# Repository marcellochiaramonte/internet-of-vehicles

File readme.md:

Internet of Vehicles Project to bring IoT into Electric Vehicles

➡️ [Micropython Pycom Module Code](./2_Software_Module)

➡️ [Fullstack Web App Springboot Angular](./3_Software_Cloud/iov-full-stack-app)

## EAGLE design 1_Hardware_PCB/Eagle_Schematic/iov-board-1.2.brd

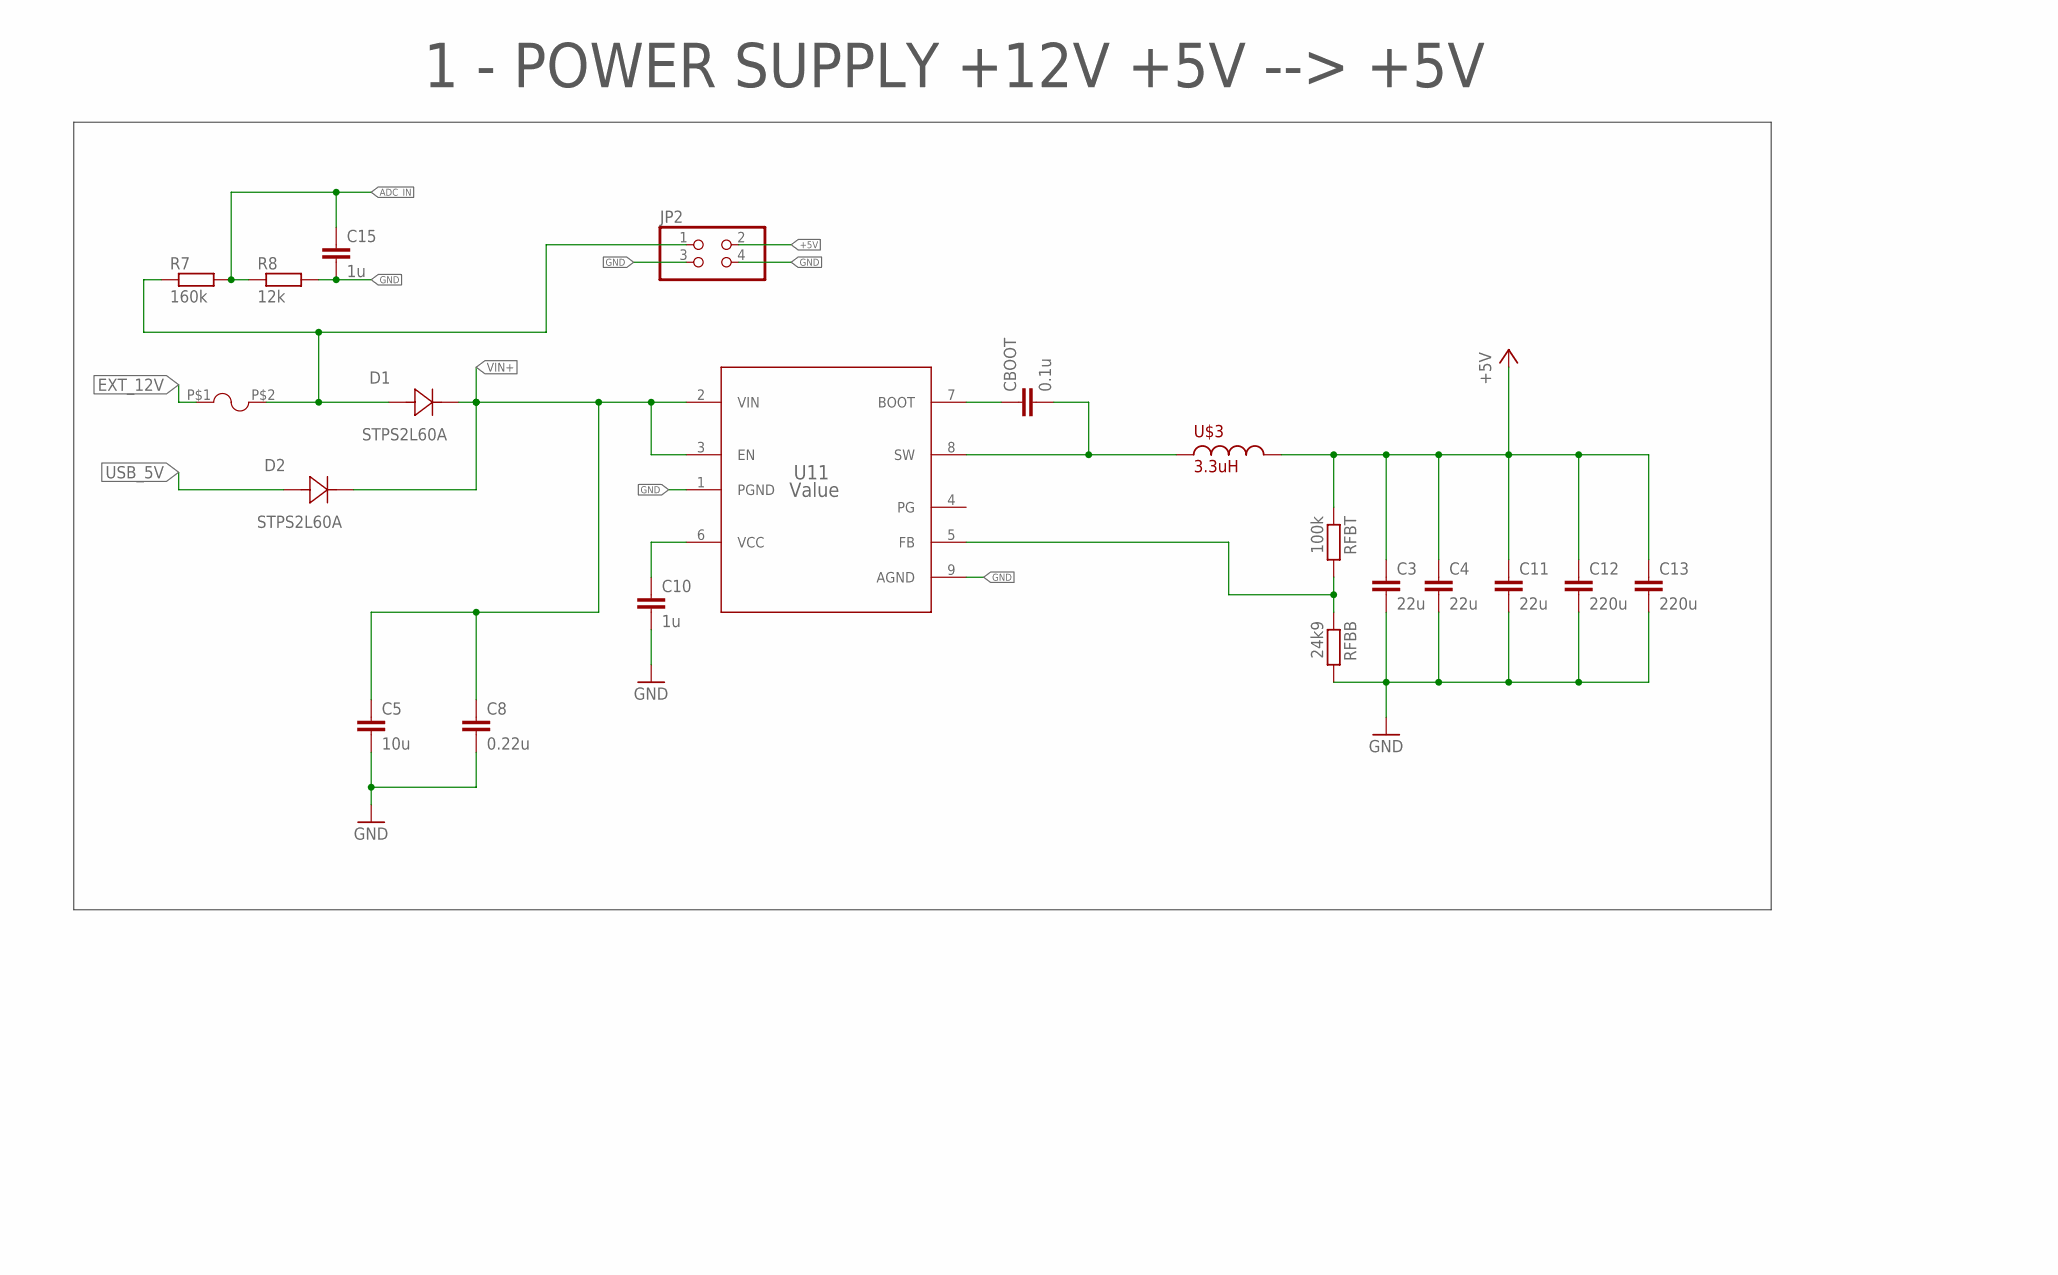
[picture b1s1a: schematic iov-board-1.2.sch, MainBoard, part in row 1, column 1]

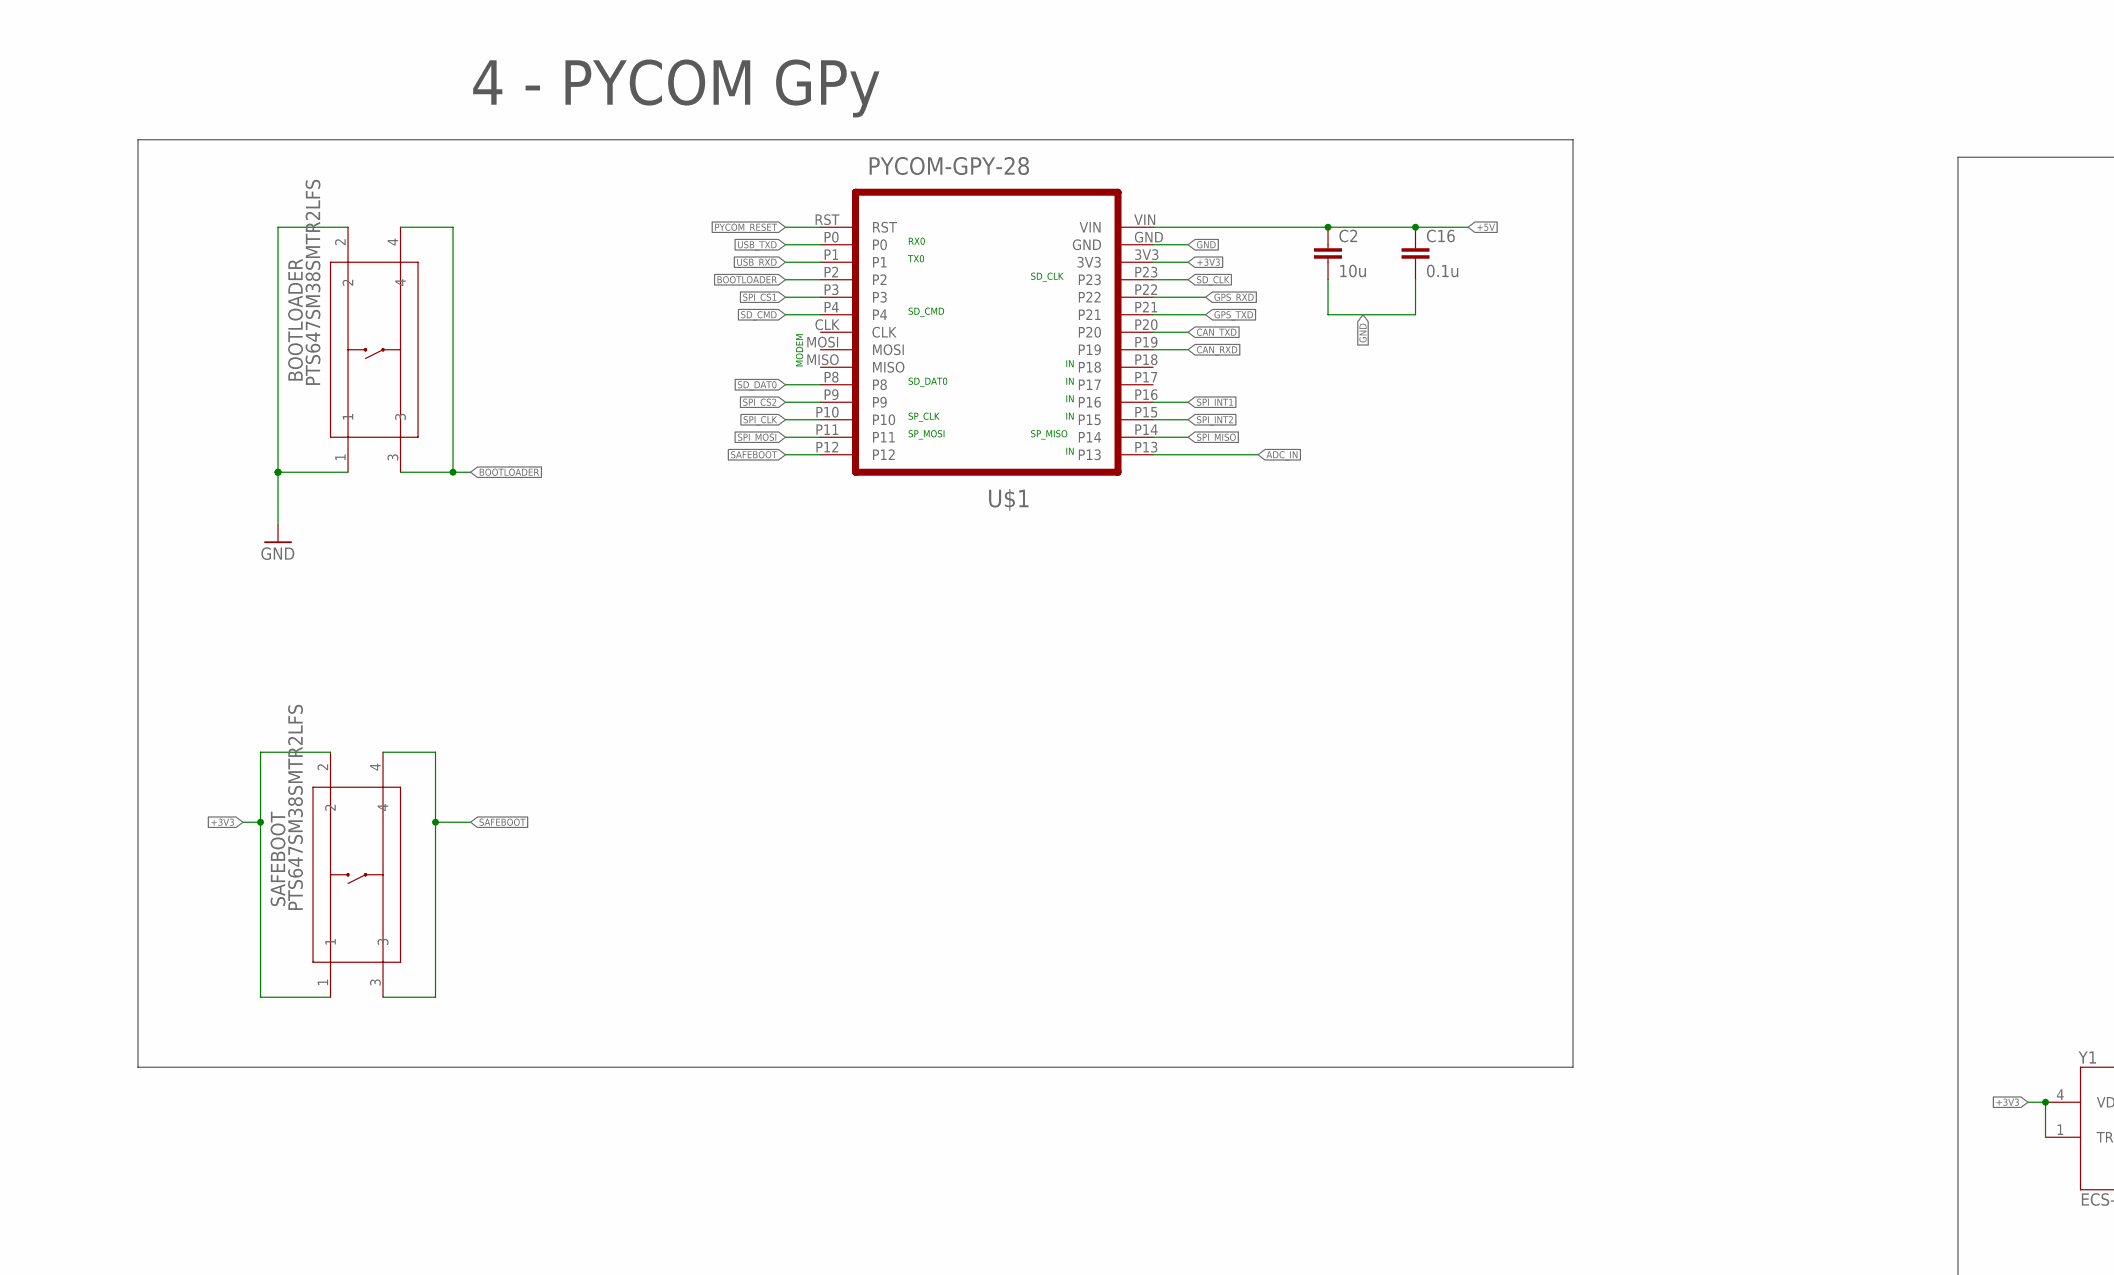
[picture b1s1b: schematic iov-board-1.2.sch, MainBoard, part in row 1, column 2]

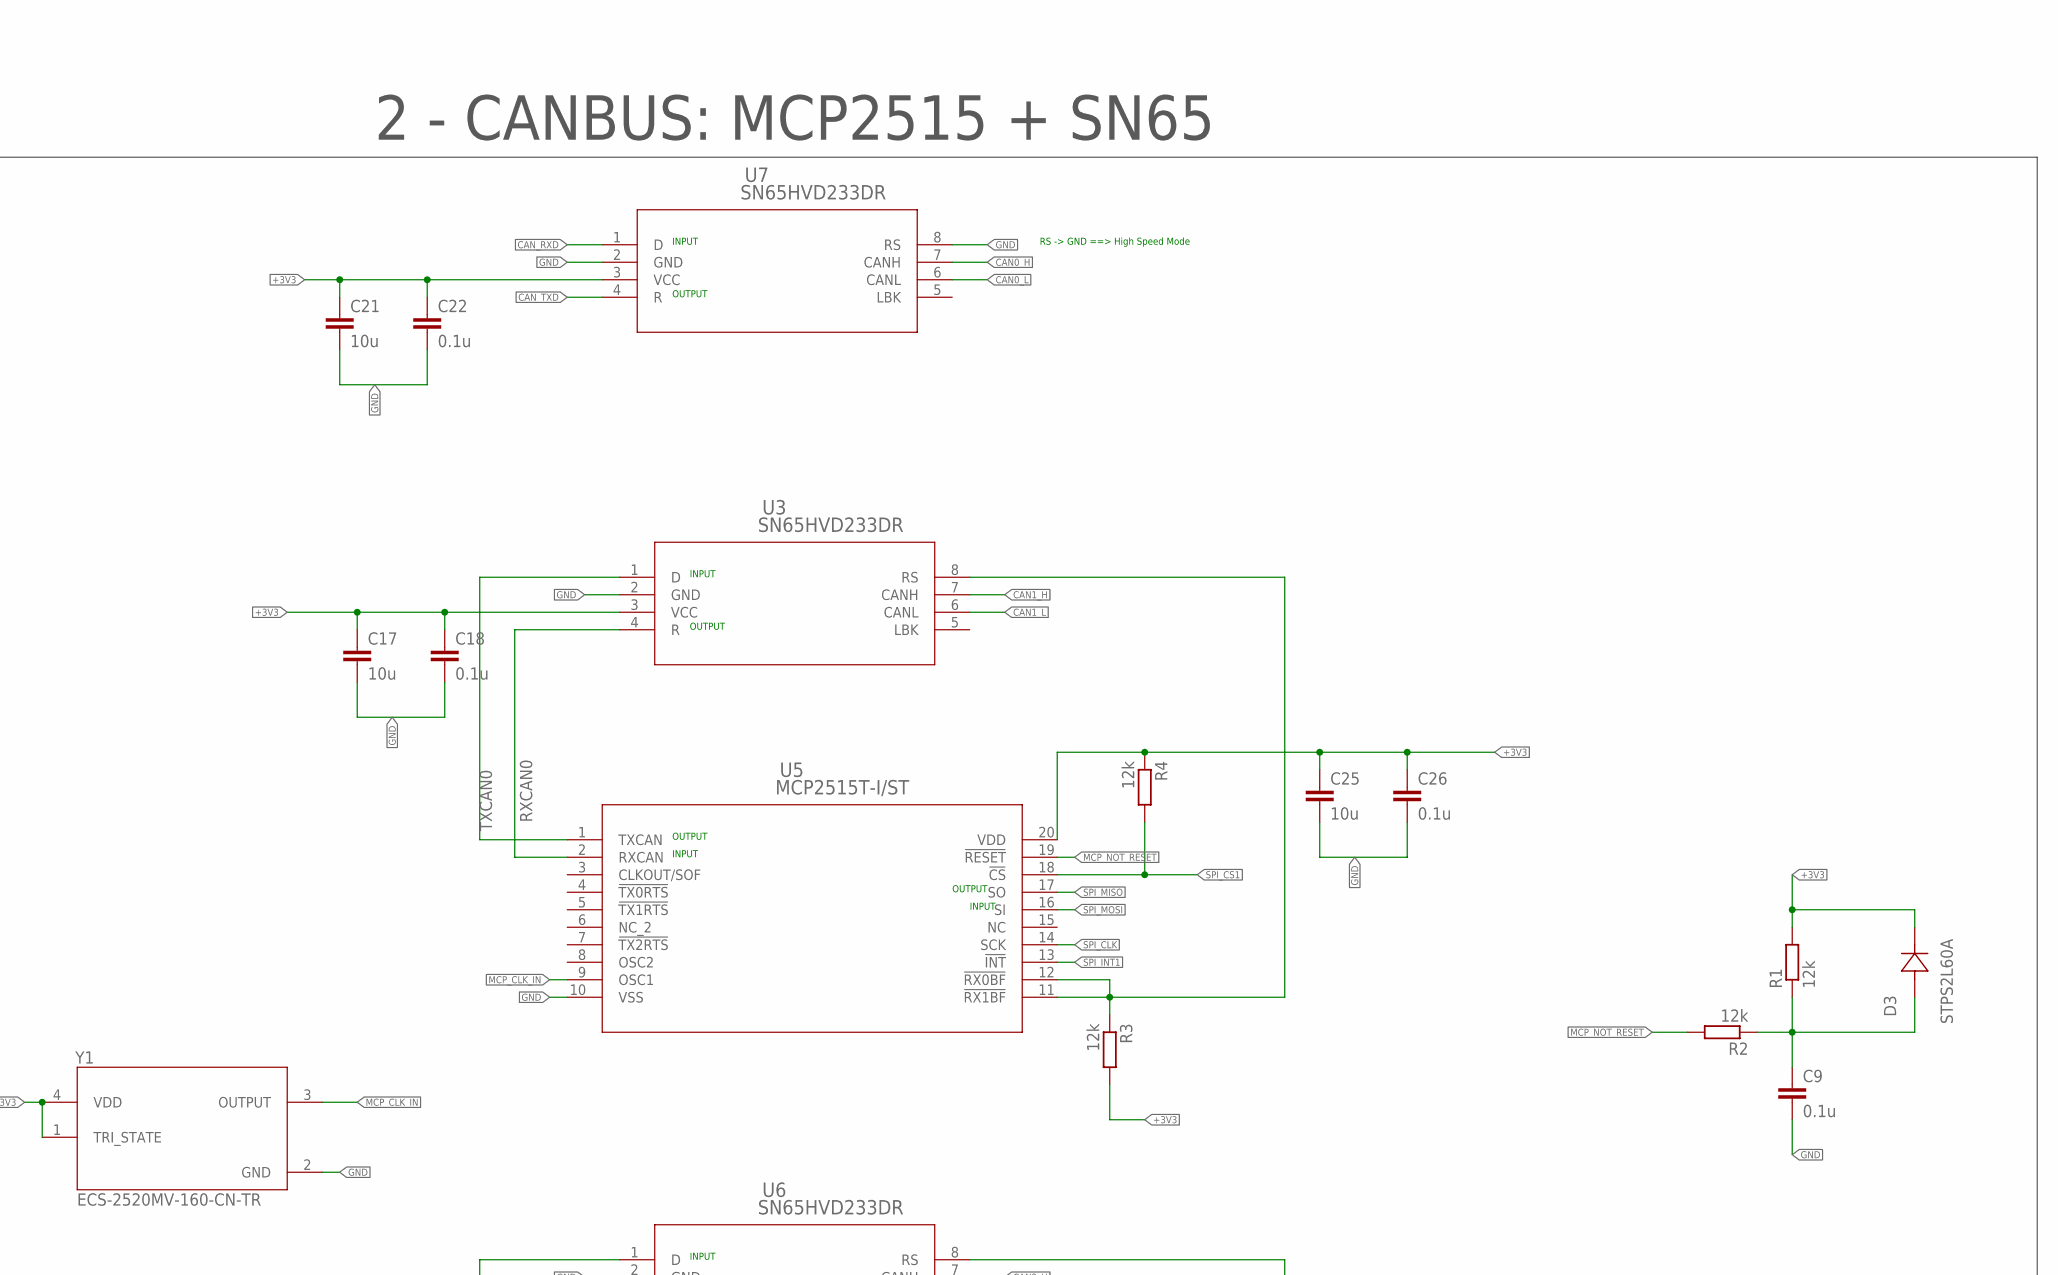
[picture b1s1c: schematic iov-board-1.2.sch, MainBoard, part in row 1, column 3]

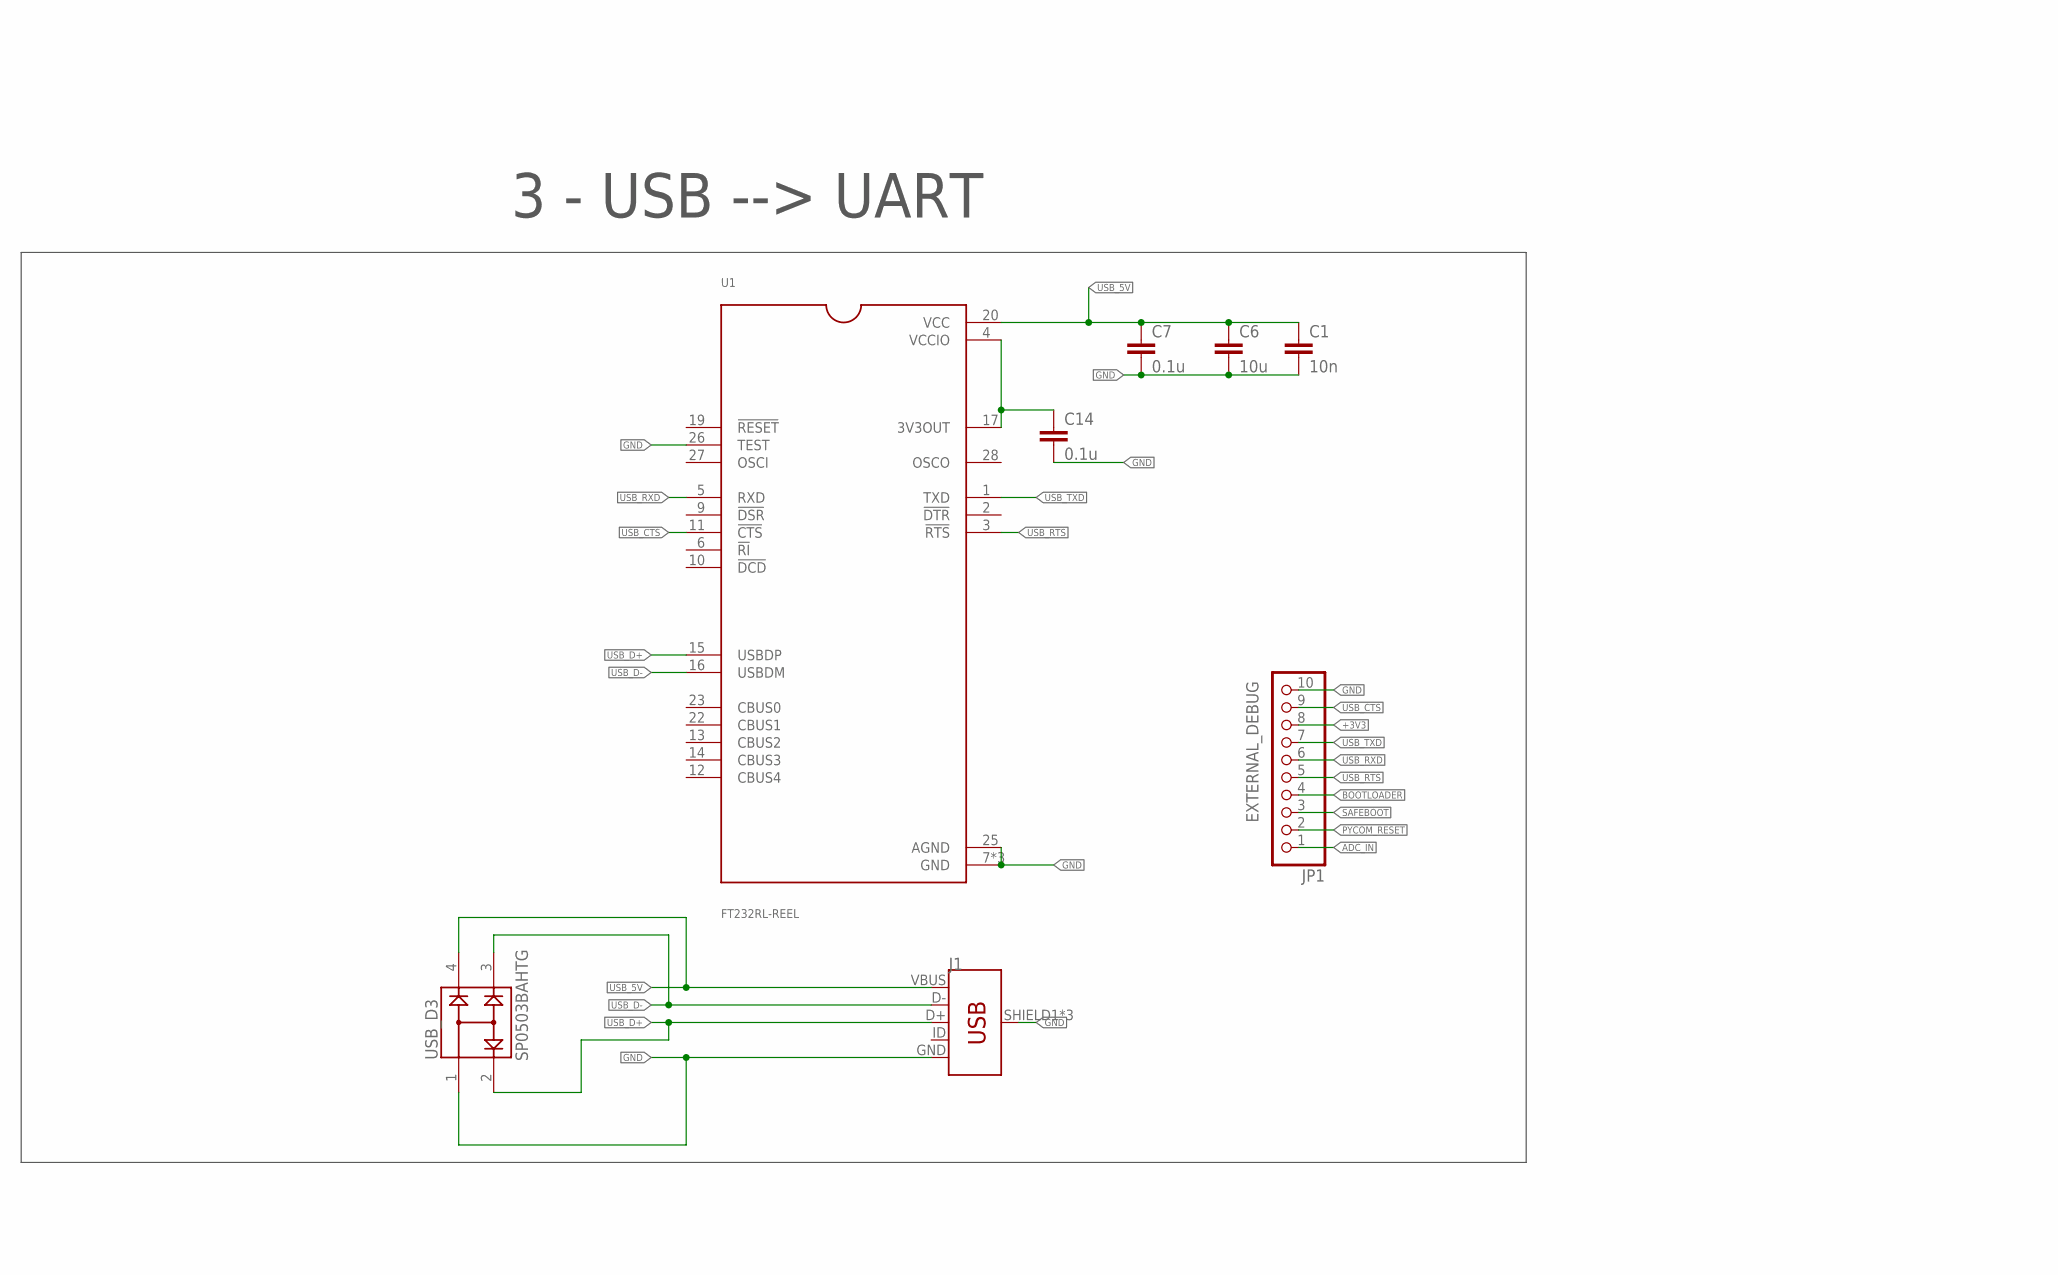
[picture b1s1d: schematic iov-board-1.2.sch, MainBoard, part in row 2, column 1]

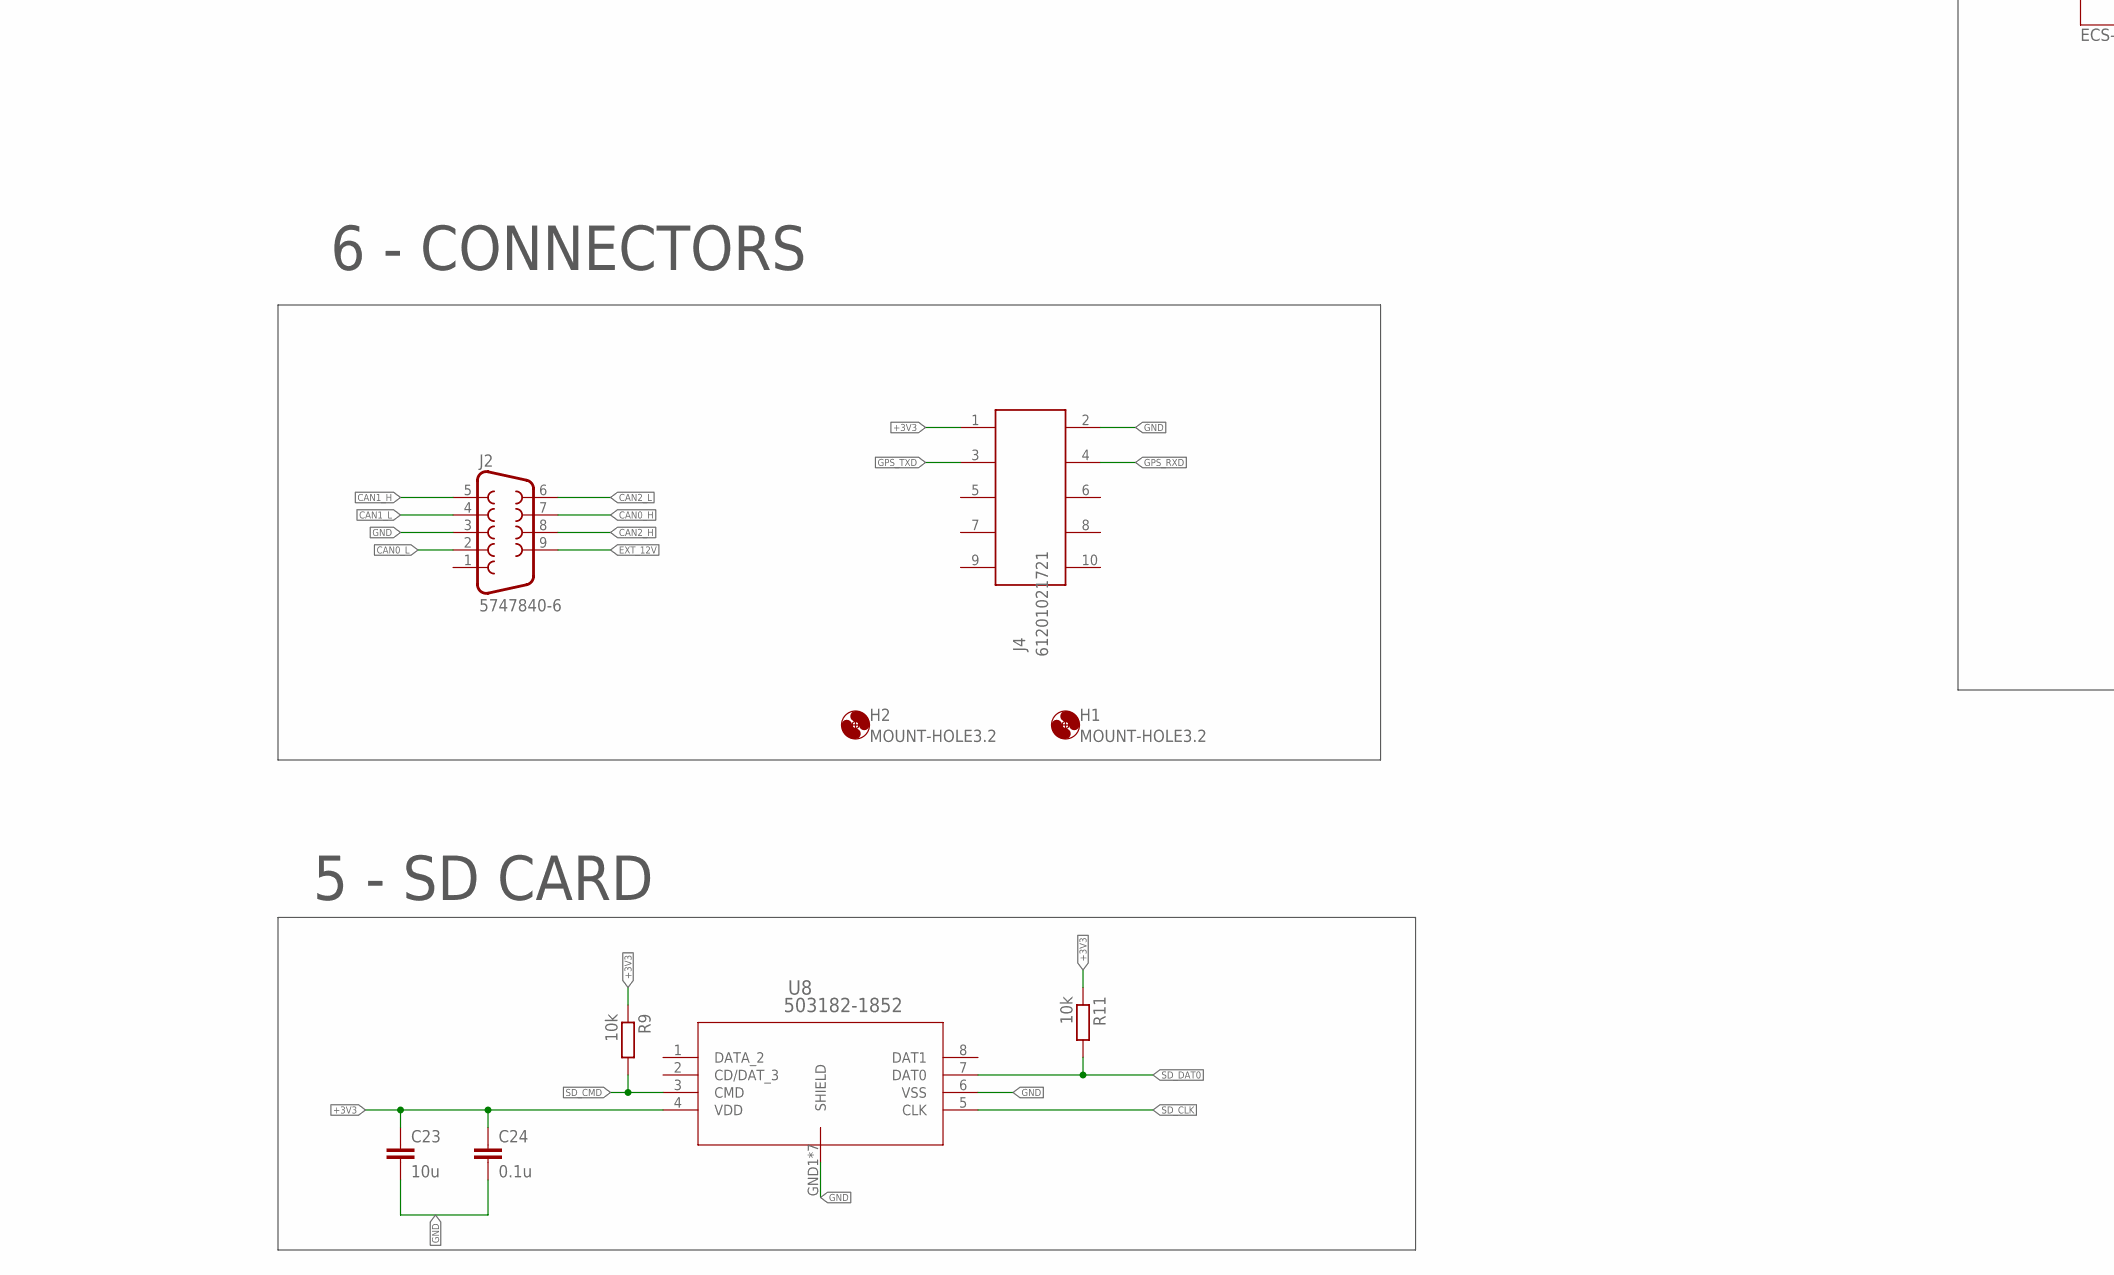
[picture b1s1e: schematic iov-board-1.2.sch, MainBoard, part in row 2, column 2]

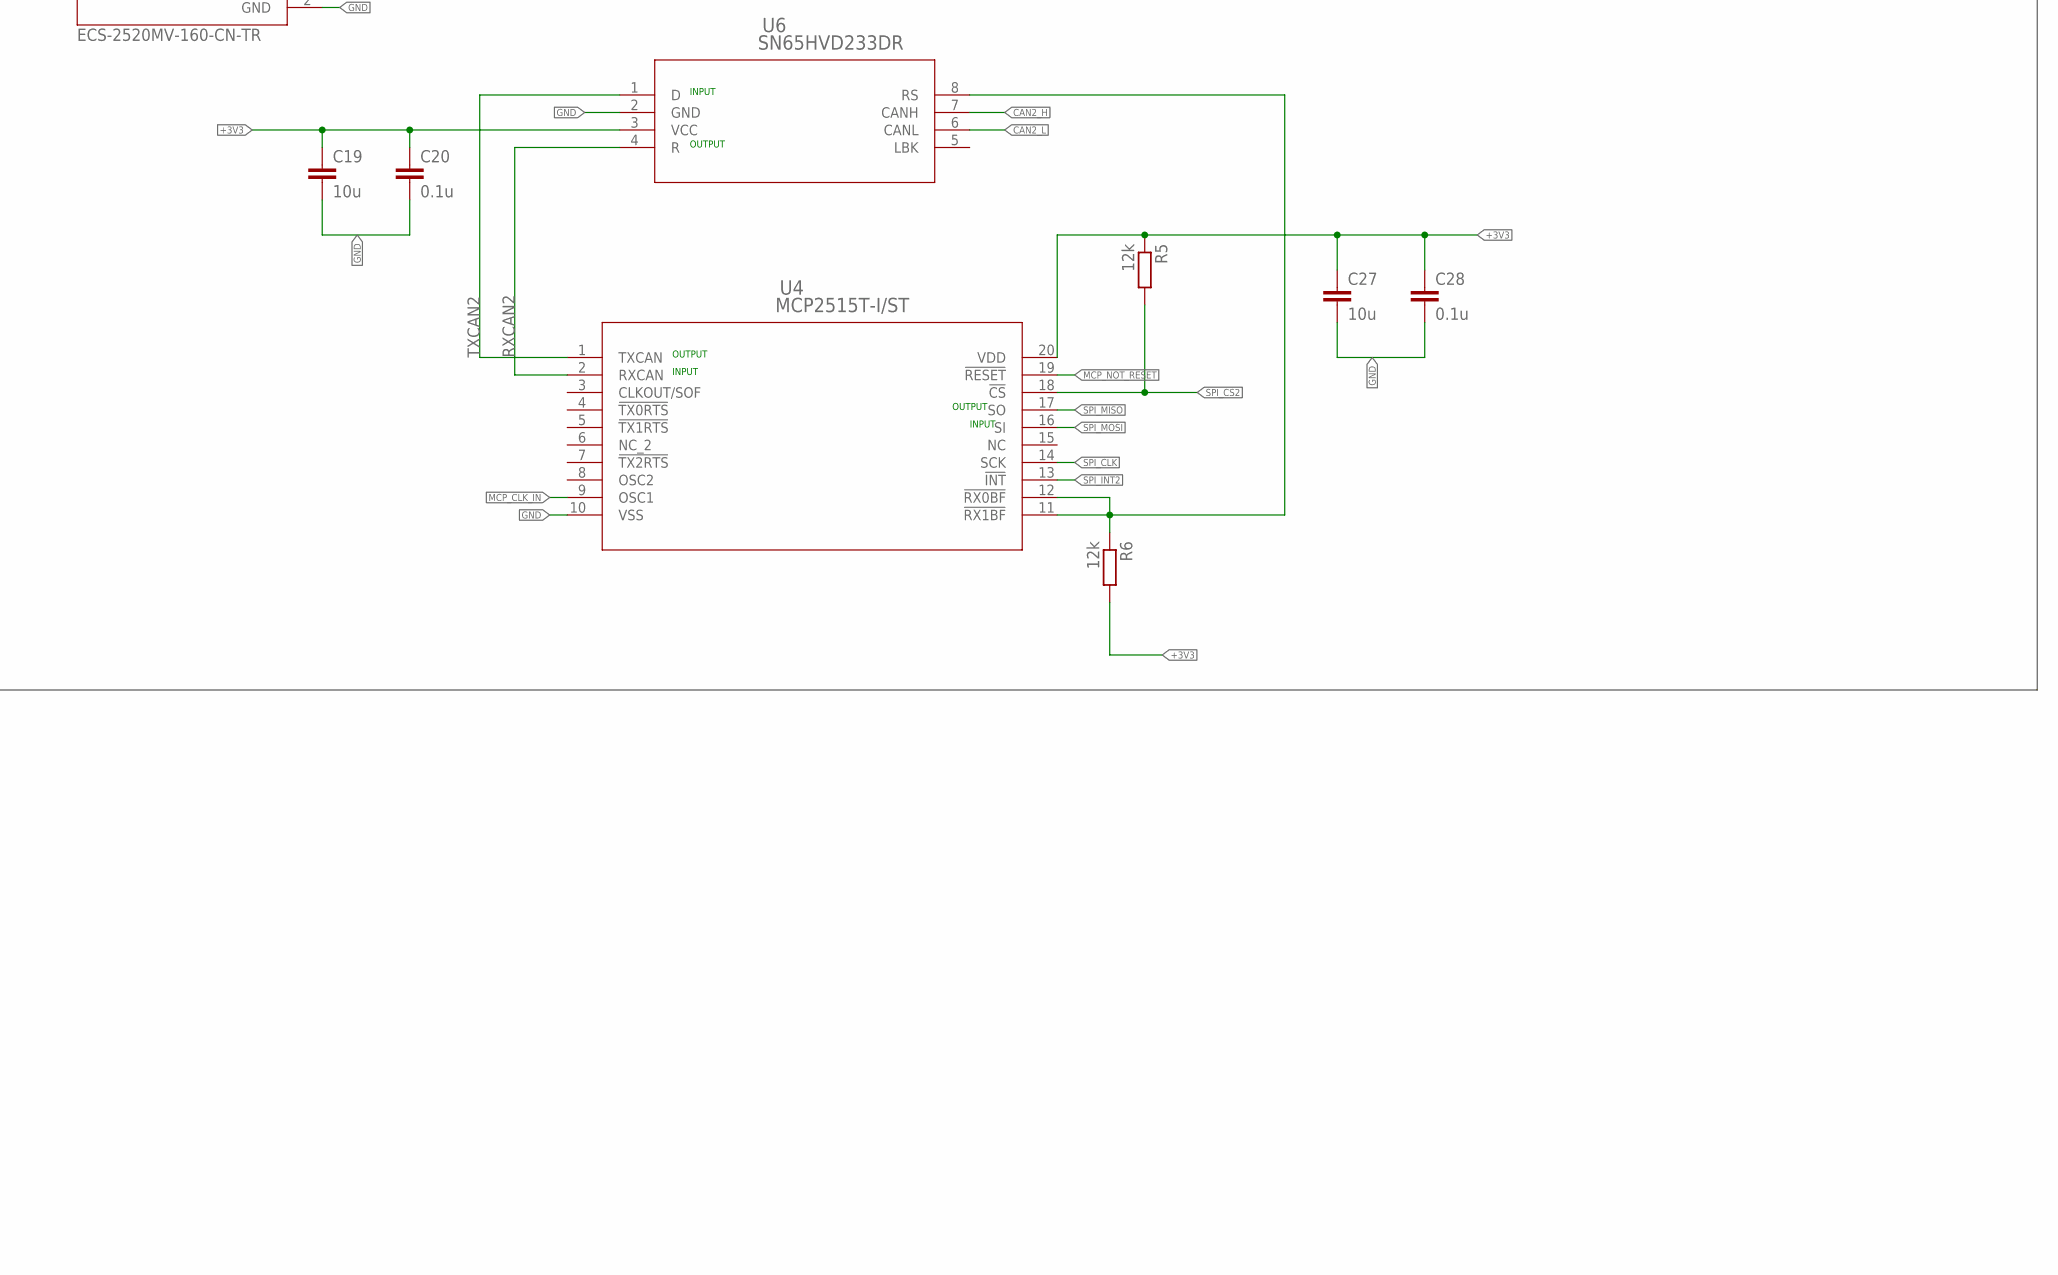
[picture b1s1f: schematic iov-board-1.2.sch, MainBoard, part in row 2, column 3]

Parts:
BOOTLOADER: PTS647SM38SMTR2LFS; SW_PTS647SM38SMTR2LFS_CNK
C1: 10n; C0805
C2, C5, C6, C17, C19, C21, C23, C25, C27: 10u; C0805
C3, C4, C11: 22u; C0805
C7, C9, C14, C16, C18, C20, C22, C24, C26, C28: 0.1u; C0805
C8: 0.22u; C0805
C10, C15: 1u; C0805
C12, C13: 220u; C1210
CBOOT: 0.1u; C0805
D1, D2, D3: STPS2L60A; SMA_STM
H1, H2: MOUNT-HOLE3.2; 3,2
J1: USB_MICRO-B_FEMALE-SMT; USB-B-MICRO-SMD
J2: 5747840-6; TE_5747840-6
J4: 61201021721
JP1: EXTERNAL_DEBUG; 1X10
JP2: PINHD-2X2; 2X02
R1, R2, R3, R4, R5, R6, R8: 12k; R0805
R7: 160k; R0805
R9, R11: 10k; R0805
RFBB: 24k9; R0805
RFBT: 100k; R0805
SAFEBOOT: PTS647SM38SMTR2LFS; SW_PTS647SM38SMTR2LFS_CNK
U1: FT232RL-REEL; SOP65P780X200-28N
U3, U6, U7: SN65HVD233DR; D8
U4, U5: MCP2515T-I/ST; TSSOP20_MC_MCH
U8: 503182-1852; 503182-1852_MOL
U11: Value; DDA0008J
U$1: PYCOM-GPY-28; PYCOM_GPY-28
U$3: 3.3uH; 3_3_UH
U$4: LITTLEFUSE_658
USB_D3: SP0503BAHTG; SOT143
Y1: ECS-2520MV-160-CN-TR; OSC_ECS-2520S25-250-FN-TR

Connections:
+3V3: C17.1, C18.1, C19.1, C20.1, C21.1, C22.1, C23.1, C24.1, C25.1, C26.1, C27.1, C28.1, D3.1, J4.1 (10), JP1.8, R1.2, R3.2, R4.1, R5.1, R6.2, R9.1, R11.1, SAFEBOOT.1, SAFEBOOT.2, U3.3 (VCC), U4.20 (VDD), U5.20 (VDD), U6.3 (VCC), U7.3 (VCC), U8.4 (VDD), U$1.3V3, Y1.1 (TRI_STATE), Y1.4 (VDD)
+5V: C2.1, C3.1, C4.1, C11.1, C12.1, C13.1, C16.1, JP2.2, RFBT.1, U$1.VIN, U$3.P$2
ADC_IN: C15.1, JP1.1, R7.2, R8.1, U$1.P13
BOOTLOADER: BOOTLOADER.3, BOOTLOADER.4, JP1.4, U$1.P2
CAN0_H: J2.7, U7.7 (CANH)
CAN0_L: J2.2, U7.6 (CANL)
CAN1_H: J2.5, U3.7 (CANH)
CAN1_L: J2.4, U3.6 (CANL)
CAN2_H: J2.8, U6.7 (CANH)
CAN2_L: J2.6, U6.6 (CANL)
CAN_RXD: U7.1 (D), U$1.P19
CAN_TXD: U7.4 (R), U$1.P20
EXT_12V: J2.9, U$4.P$1
FB1: RFBB.1, RFBT.2, U11.5 (FB)
GND: BOOTLOADER.1, BOOTLOADER.2, C1.2, C2.2, C3.2, C4.2, C5.2, C6.2, C7.2, C8.2, C9.2, C10.2, C11.2, C12.2, C13.2, C14.2, C15.2, C16.2, C17.2, C18.2, C19.2, C20.2, C21.2, C22.2, C23.2, C24.2, C25.2, C26.2, C27.2, C28.2, J1.GND, J1.SHIELD1 (SHIELD), J1.SHIELD2 (SHIELD), J1.SHIELD3 (SHIELD), J2.3, J4.2 (9), JP1.10, JP2.3, JP2.4, R8.2, RFBB.2, U1.7 (GND), U1.18 (GND), U1.21 (GND), U1.25 (AGND), U1.26 (TEST), U3.2 (GND), U4.10 (VSS), U5.10 (VSS), U6.2 (GND), U7.2 (GND), U7.8 (RS), U8.6 (VSS), U8.GND1 (SHIELD), U8.GND2 (SHIELD), U8.GND3 (SHIELD), U8.GND4 (SHIELD), U8.GND5 (SHIELD), U8.GND6 (SHIELD), U8.GND7 (SHIELD), U11.1 (PGND), U11.9 (AGND), U$1.GND, USB_D3.1, Y1.2 (GND)
GPS_RXD: J4.4 (7), U$1.P22
GPS_TXD: J4.3 (8), U$1.P21
MCP_CLK_IN: U4.9 (OSC1), U5.9 (OSC1), Y1.3 (OUTPUT)
MCP_NOT_RESET: R2.2, U4.19 (!RESET), U5.19 (!RESET)
unnamed: C10.1, U11.6 (VCC)
unnamed: C14.1, U1.4 (VCCIO), U1.17 (3V3OUT)
unnamed: C9.1, D3.2, R1.1, R2.1
unnamed: D1.2, JP2.1, R7.1, U$4.P$2
unnamed: CBOOT.2, U11.8 (SW), U$3.P$1
unnamed: CBOOT.1, U11.7 (BOOT)
unnamed: R6.1, U4.11 (!RX1BF), U4.12 (!RX0BF), U6.8 (RS)
unnamed: R3.1, U3.8 (RS), U5.11 (!RX1BF), U5.12 (!RX0BF)
PYCOM_RESET: JP1.2, U$1.RST
RXCAN0: U3.4 (R), U5.2 (RXCAN)
RXCAN2: U4.2 (RXCAN), U6.4 (R)
SAFEBOOT: JP1.3, SAFEBOOT.3, SAFEBOOT.4, U$1.P12
SD_CLK: U8.5 (CLK), U$1.P23
SD_CMD: R9.2, U8.3 (CMD), U$1.P4
SD_DAT0: R11.2, U8.7 (DAT0), U$1.P8
SPI_CLK: U4.14 (SCK), U5.14 (SCK), U$1.P10
SPI_CS1: R4.2, U5.18 (!CS), U$1.P3
SPI_CS2: R5.2, U4.18 (!CS), U$1.P9
SPI_INT1: U5.13 (!INT), U$1.P16
SPI_INT2: U4.13 (!INT), U$1.P15
SPI_MISO: U4.17 (SO), U5.17 (SO), U$1.P14
SPI_MOSI: U4.16 (SI), U5.16 (SI), U$1.P11
TXCAN0: U3.1 (D), U5.1 (TXCAN)
TXCAN2: U4.1 (TXCAN), U6.1 (D)
USB_5V: C1.1, C6.1, C7.1, D2.2, J1.VBUS, U1.20 (VCC), USB_D3.4
USB_CTS: JP1.9, U1.11 (!CTS)
USB_D+: J1.D+, U1.15 (USBDP), USB_D3.2
USB_D-: J1.D-, U1.16 (USBDM), USB_D3.3
USB_RTS: JP1.5, U1.3 (!RTS)
USB_RXD: JP1.6, U1.5 (RXD), U$1.P1
USB_TXD: JP1.7, U1.1 (TXD), U$1.P0
VIN+: C5.1, C8.1, D1.1, D2.1, U11.2 (VIN), U11.3 (EN)

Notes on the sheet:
2 - CANBUS: MCP2515 + SN65
6 - CONNECTORS
4 - PYCOM GPy
5 - SD CARD
1 - POWER SUPPLY +12V +5V --> +5V
3 - USB --> UART
SD_CMD
RX0
TX0
SD_DAT0
SD_CLK
SP_MISO
MODEM
SP_CLK
SP_MOSI
INPUT
OUTPUT
RS -> GND ==> High Speed Mode

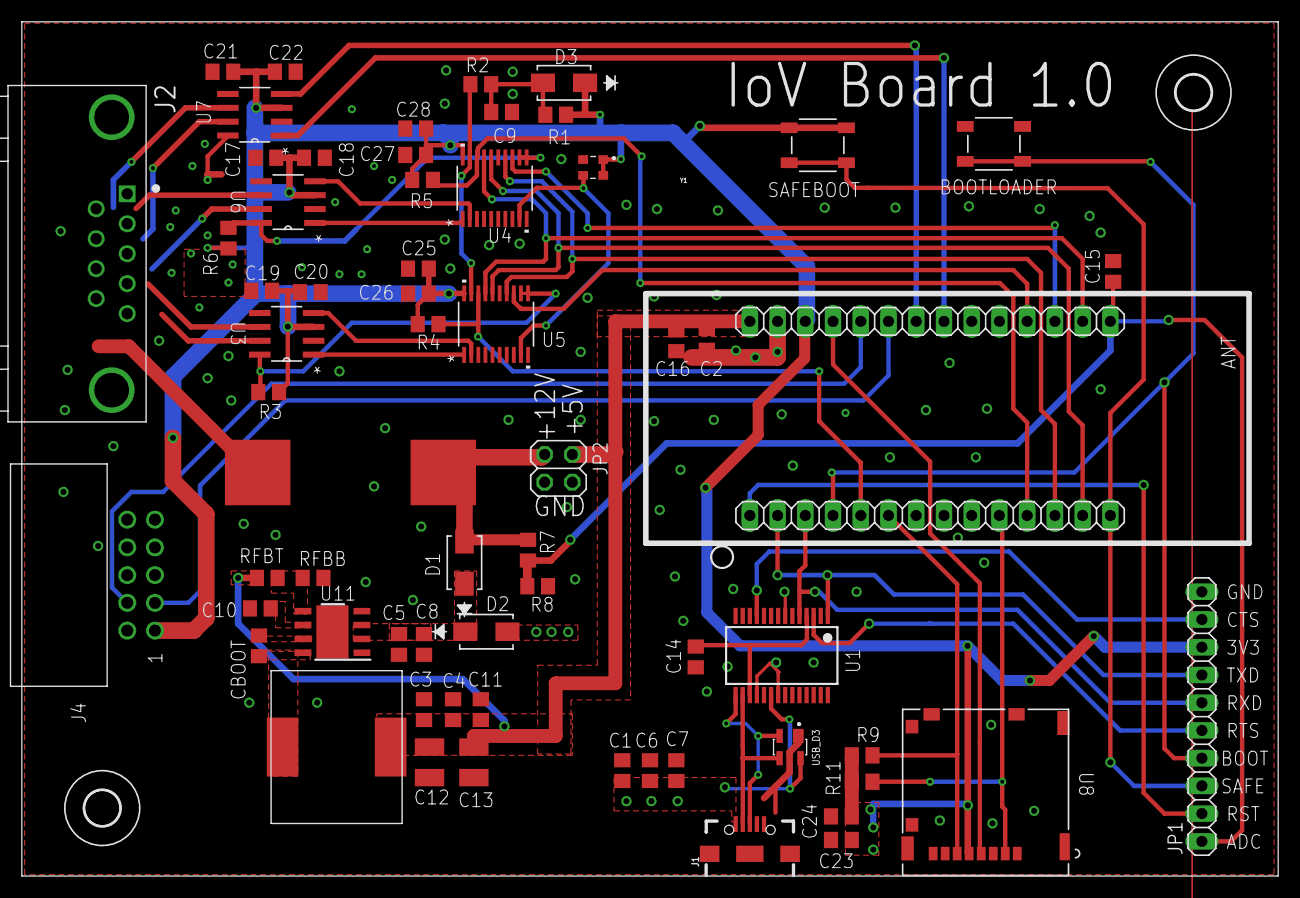
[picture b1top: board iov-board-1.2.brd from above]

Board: 2 copper layers, 115.1 x 78.2 mm, 66 parts (0 on the bottom side), 51 nets.

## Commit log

2025-03-21 Added BachelorArbeit

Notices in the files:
parts and their libraries:
SparkFun-Connectors_usb: Licensing: Creative Commons ShareAlike 4.0 International - https://creativecommons.org/licenses/by-sa/4.0
COPYRIGHT: Copyright (C) 2018 Accelerated Designs. All rights reserved
